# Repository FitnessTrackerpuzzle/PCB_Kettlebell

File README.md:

# PCB_Kettlebell
Hier zijn de kicad-files (voor het ontwikkelen van de PCB die aan de ketllebell hangt) terug te vinden. Ook zijn hier de STL-files van het beschermdoosje terug te vinden.

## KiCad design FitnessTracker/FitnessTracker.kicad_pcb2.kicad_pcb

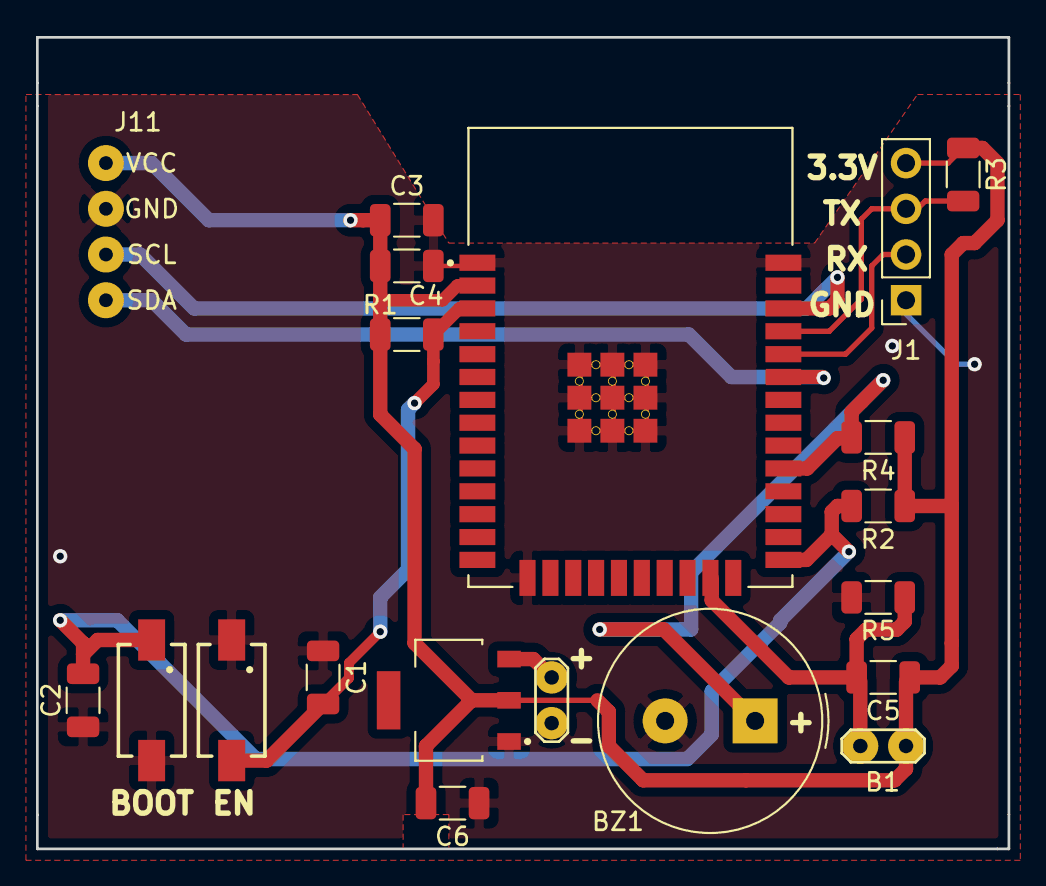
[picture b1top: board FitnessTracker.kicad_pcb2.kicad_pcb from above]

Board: 2 copper layers, 54.0 x 45.1 mm, 20 parts (0 on the bottom side), 11 nets.

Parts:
 : Conn_01x02_Female; TestPoint_2Pads_Pitch2.54mm_Drill0.8mm
 #2: SOT229P700X180-4N
 #3: MODULE_ESP32-WROOM-32E_(16MB)
 #4,  #5: 434111043826
B1: Button; TestPoint_2Pads_Pitch2.54mm_Drill0.8mm
BZ1: Buzzer; Buzzer_TDK_PS1240P02BT_D12.2mm_H6.5mm
C1, C2, C3, C4, C5: 100nF; C_1206_3216Metric
C6: 10µ; C_1206_3216Metric
J1: Conn_01x04_Female; PinSocket_1x04_P2.54mm_Vertical
J11: MPU9250; MPU_9250
R1, R2, R3, R4: 4.7k; C_1206_3216Metric
R5: 330; C_1206_3216Metric

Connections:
GND: .2, #2.1, #3.1, #3.15, #3.38, #3.39_1, #3.39_2, #3.39_3, #3.39_4, #3.39_5, #3.39_6, #3.39_7, #3.39_8, #3.39_9, #3.39_10, #3.39_11, #3.39_12, #3.39_13, #3.39_14, #3.39_15, #3.39_16, #3.39_17, #3.39_18, #3.39_19, #3.39_20, #3.39_21, #4.2, #5.1, BZ1.2, C1.1, C2.2, C3.2, C4.2, C6.1, J1.1, J11.2, R5.2
unnamed: #2.2, #3.2, B1.1, C3.1, C4.1, C5.1, C6.2, J1.4, J11.1, R1.1, R2.1, R3.1, R4.1
unnamed: #3.23, B1.2, C5.2, R5.1
unnamed: #3.29, BZ1.1, R4.2
unnamed: #3.3, #5.2, C1.2, R1.2
unnamed: #3.25, #4.1, C2.1, R2.2
unnamed: #3.34, J1.2
unnamed: #3.35, J1.3, R3.2
unnamed: #3.36, J11.3
unnamed: #3.33, J11.4
unnamed: .1, #2.3
